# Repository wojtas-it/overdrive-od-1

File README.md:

# OverDrive Unit OD-1

An analog guitar overdrive/distortion pedal built around a dual op-amp gain stage and diode clipping.

## Circuit overview

The signal path follows a classic op-amp overdrive topology, similar in spirit to circuits like the Tube Screamer: an op-amp gain stage feeding a diode clipper, followed by a passive tone filter and a buffered output stage.

- **Input stage** - high impedance input (1 MOhm), AC-coupled with a 100 nF capacitor so the pedal doesn't load down the guitar's pickups.
- **Gain stage** - one half of a TL072 op-amp, with the GAIN pot (100 kOhm) in the feedback path. Gain is adjustable roughly from unity up to around 100x.
- **Clipping stage** - two 1N4148 diodes wired anti-parallel to virtual ground, symmetrically clipping the signal at about +/-0.7 V. This is what generates the overdrive harmonics.
- **Tone stage** - a passive RC low-pass filter with a 100 kOhm TONE pot, shaping the signal from dark to bright.
- **Output stage** - the second half of the TL072 as a buffer/gain stage with the VOLUME pot (100 kOhm log), followed by an output coupling capacitor and a low output impedance (under 1 kOhm) so it can drive an amp or the next pedal in the chain.
- **Power** - runs from a single 9V supply (battery or DC adapter). A resistor divider plus a third TL072 buffer generates a virtual ground at 4.5 V so the op-amps can work single-supply. Current draw is under 10 mA.

Full details, block diagram, and the BOM are in [docs](docs).

Note: the docs were submitted as a two-person university assignment, so a partner's name appears on them alongside mine. In practice I designed and built this alone; the partner didn't contribute.

## Tools

- KiCad 9.0.5 for schematic capture and PCB layout
- Standard KiCad libraries only (Device, Amplifier_Operational, Diode, Connector, Connector_Audio, power) - no custom parts, so the project opens without missing library errors

## Status

- Schematic: complete, passes ERC with 0 errors and 0 warnings
- PCB layout: complete, 2-layer board, routed
- Physical build: not yet built, so there's no prototype photo yet
- Testing: not yet documented

The schematic and PCB layout above are exported from the KiCad files in [kicad](kicad). A photo of the physical pedal will be added here once it's built.

Designed in 2026 as a university electronics project.

## More

Portfolio: [wojtas.it](https://wojtas.it)

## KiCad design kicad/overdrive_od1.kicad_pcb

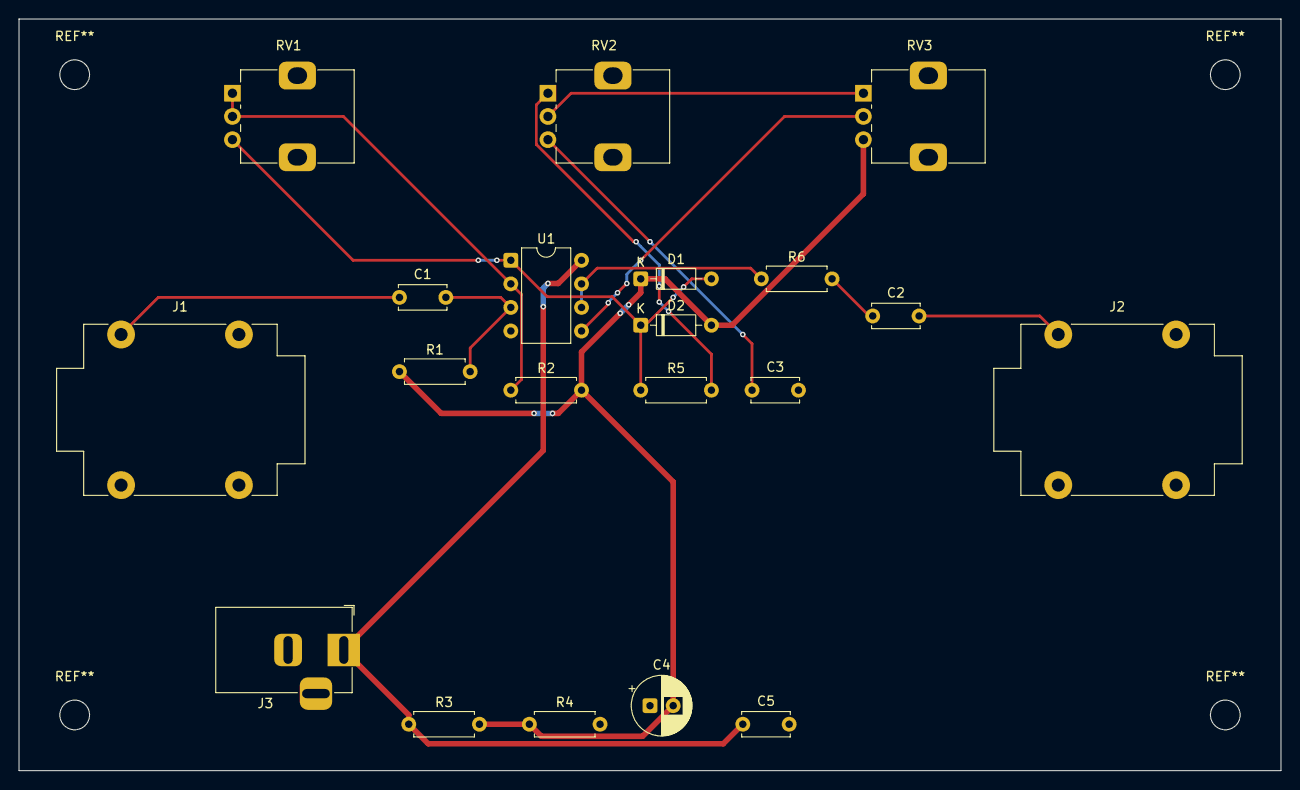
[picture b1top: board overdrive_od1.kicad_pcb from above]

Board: 2 copper layers, 136.0 x 81.0 mm, 20 parts (0 on the bottom side), 14 nets.

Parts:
C1, C2, C5: 100nF; C_Disc_D5.0mm_W2.5mm_P5.00mm
C3: 47nF; C_Disc_D5.0mm_W2.5mm_P5.00mm
C4: 100µF; CP_Radial_D6.3mm_P2.50mm
D1, D2: 1N4148; D_DO-35_SOD27_P7.62mm_Horizontal
J1, J2: AudioJack2_SwitchT; Jack_6.35mm_Neutrik_NMJ4HCD2_Horizontal
J3: Barrel_Jack_Switch; BarrelJack_Horizontal
R1: 1MΩ; R_Axial_DIN0207_L6.3mm_D2.5mm_P7.62mm_Horizontal
R2: 4.7kΩ; R_Axial_DIN0207_L6.3mm_D2.5mm_P7.62mm_Horizontal
R3, R4, R5: 10kΩ; R_Axial_DIN0207_L6.3mm_D2.5mm_P7.62mm_Horizontal
R6: 1kΩ; R_Axial_DIN0207_L6.3mm_D2.5mm_P7.62mm_Horizontal
RV1, RV2, RV3: 100kΩ; Potentiometer_Alps_RK09K_Single_Vertical
U1: TL072; DIP-8_W7.62mm

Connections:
/+9V: C5.1, J3.1, R3.1, U1.8 (V+)
/GAINFB: R2.1, RV1.1, RV1.2, U1.2 (-)
/U1BOUT: R6.1, U1.6 (-), U1.7
/VG: C4.2, D1.1 (K), D2.2 (A), R1.1, R2.2, R3.2, R4.1, RV3.3
/VOLIN: RV2.2, RV3.1
/VOLW: RV3.2, U1.5 (+)
GND: C3.2, C4.1, C5.2, J1.S, J2.S, J3.2, R4.2, U1.4 (V-)
unnamed: C1.1, J1.T
unnamed: C2.1, R6.2
unnamed: C2.2, J2.T
unnamed: C3.1, RV2.3
unnamed: D1.2 (A), D2.1 (K), R5.1, RV1.3, U1.1
unnamed: R5.2, RV2.1
unnamed: C1.2, R1.2, U1.3 (+)
